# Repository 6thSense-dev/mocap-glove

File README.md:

# 6thSense magnetic MoCap glove

STM32G474 diagnostic/streaming firmware and local magnetic fingertip tracking viewer.

## Run locally

Install Python dependencies with `python3 -m pip install -r requirements.txt`, then run `python3 control-panel/server.py` and open http://127.0.0.1:8775/hand.

Read START-HERE.txt before powered tests. Firmware build instructions are in firmware-app/BUILD.txt. The viewer does not automatically flash hardware.

## Saved scope and limitations

Includes firmware source, local viewer, calibration algorithms, automated tests and required vendor assets. Hardware-specific calibration profiles, recordings, flash backups and build outputs remain on the development machine and are intentionally excluded. An empty checkout requires its own calibration before calibrated tracking can be reproduced. Browser display preferences are local to the browser.

Jitter filtering, continuous mirror-branch tracking and reversible per-finger Z display correction are included. Z reversal is a display correction, not physical calibration. Magnetic mirror ambiguity and absolute accuracy are not established by software tests. IMU translation is experimental and drifts; CAD joint angles are inferred robot retargeting, not independently measured finger joints.

## Third-party assets

The Aero Hand Open meshes and URDF originate from Chestnut Robotics (formerly TetherIA), commit 7bb2f23485a7d440960c21046da642de132b7745, under CC BY-NC-SA 4.0. Preserve the license, attribution and provenance in control-panel/vendor/aero-hand/. The current integration is for the user-confirmed noncommercial use. This is not a blanket license for commercial use of those assets.

Three.js and ST firmware dependencies retain their upstream license files. No blanket license is granted over the entire repository.

## Tests

`python3 -m unittest discover -s control-panel -p 'test_*.py'`

`node control-panel/test-hand-z-reflection.cjs`

`node control-panel/test-aero-kinematics.cjs`

`node control-panel/test-hand-view-frame.cjs`

## PCB design files

[Complete V6 PCB projects and manufacturing files](hardware/pcb/v6/README.md): hand hub, fingertip flex and source carrier.

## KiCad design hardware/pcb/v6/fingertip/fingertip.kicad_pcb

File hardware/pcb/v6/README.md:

# V6 PCB design archive

Complete current V6 project files for the hand hub, fingertip flex board and source carrier. Open each folder's `.kicad_pro` in KiCad 9. Custom symbols, footprints and envelope models are included; standard 3D models require KiCad's standard model library.

Each board includes schematics, routed PCB, project settings, local libraries, BOM, placement CSV, Gerber/drill files and ZIP, fabrication notes, rendered views and historical ERC/DRC reports. Source-carrier is included as a design artifact; it is not proof of the current hand-wound coil assembly configuration.

This is an archive of the existing V6 design, not a new engineering release or a renewed validation. Historical notes and reports reflect their original dates. In particular, the fingertip fabrication data specifies 0.40 mm FR4 stiffening; confirm the manufacturer-approved stackup before reordering. Do not infer measured tracking accuracy or factory acceptance from these files.

Order/checkout records, private contact details, editor state, obsolete V1–V5 designs and software recordings are excluded. Only machine-specific paths in exported verification netlists were made relative; electrical design and manufacturing files are unchanged. FILE-MANIFEST.json records SHA-256 hashes of the published files.

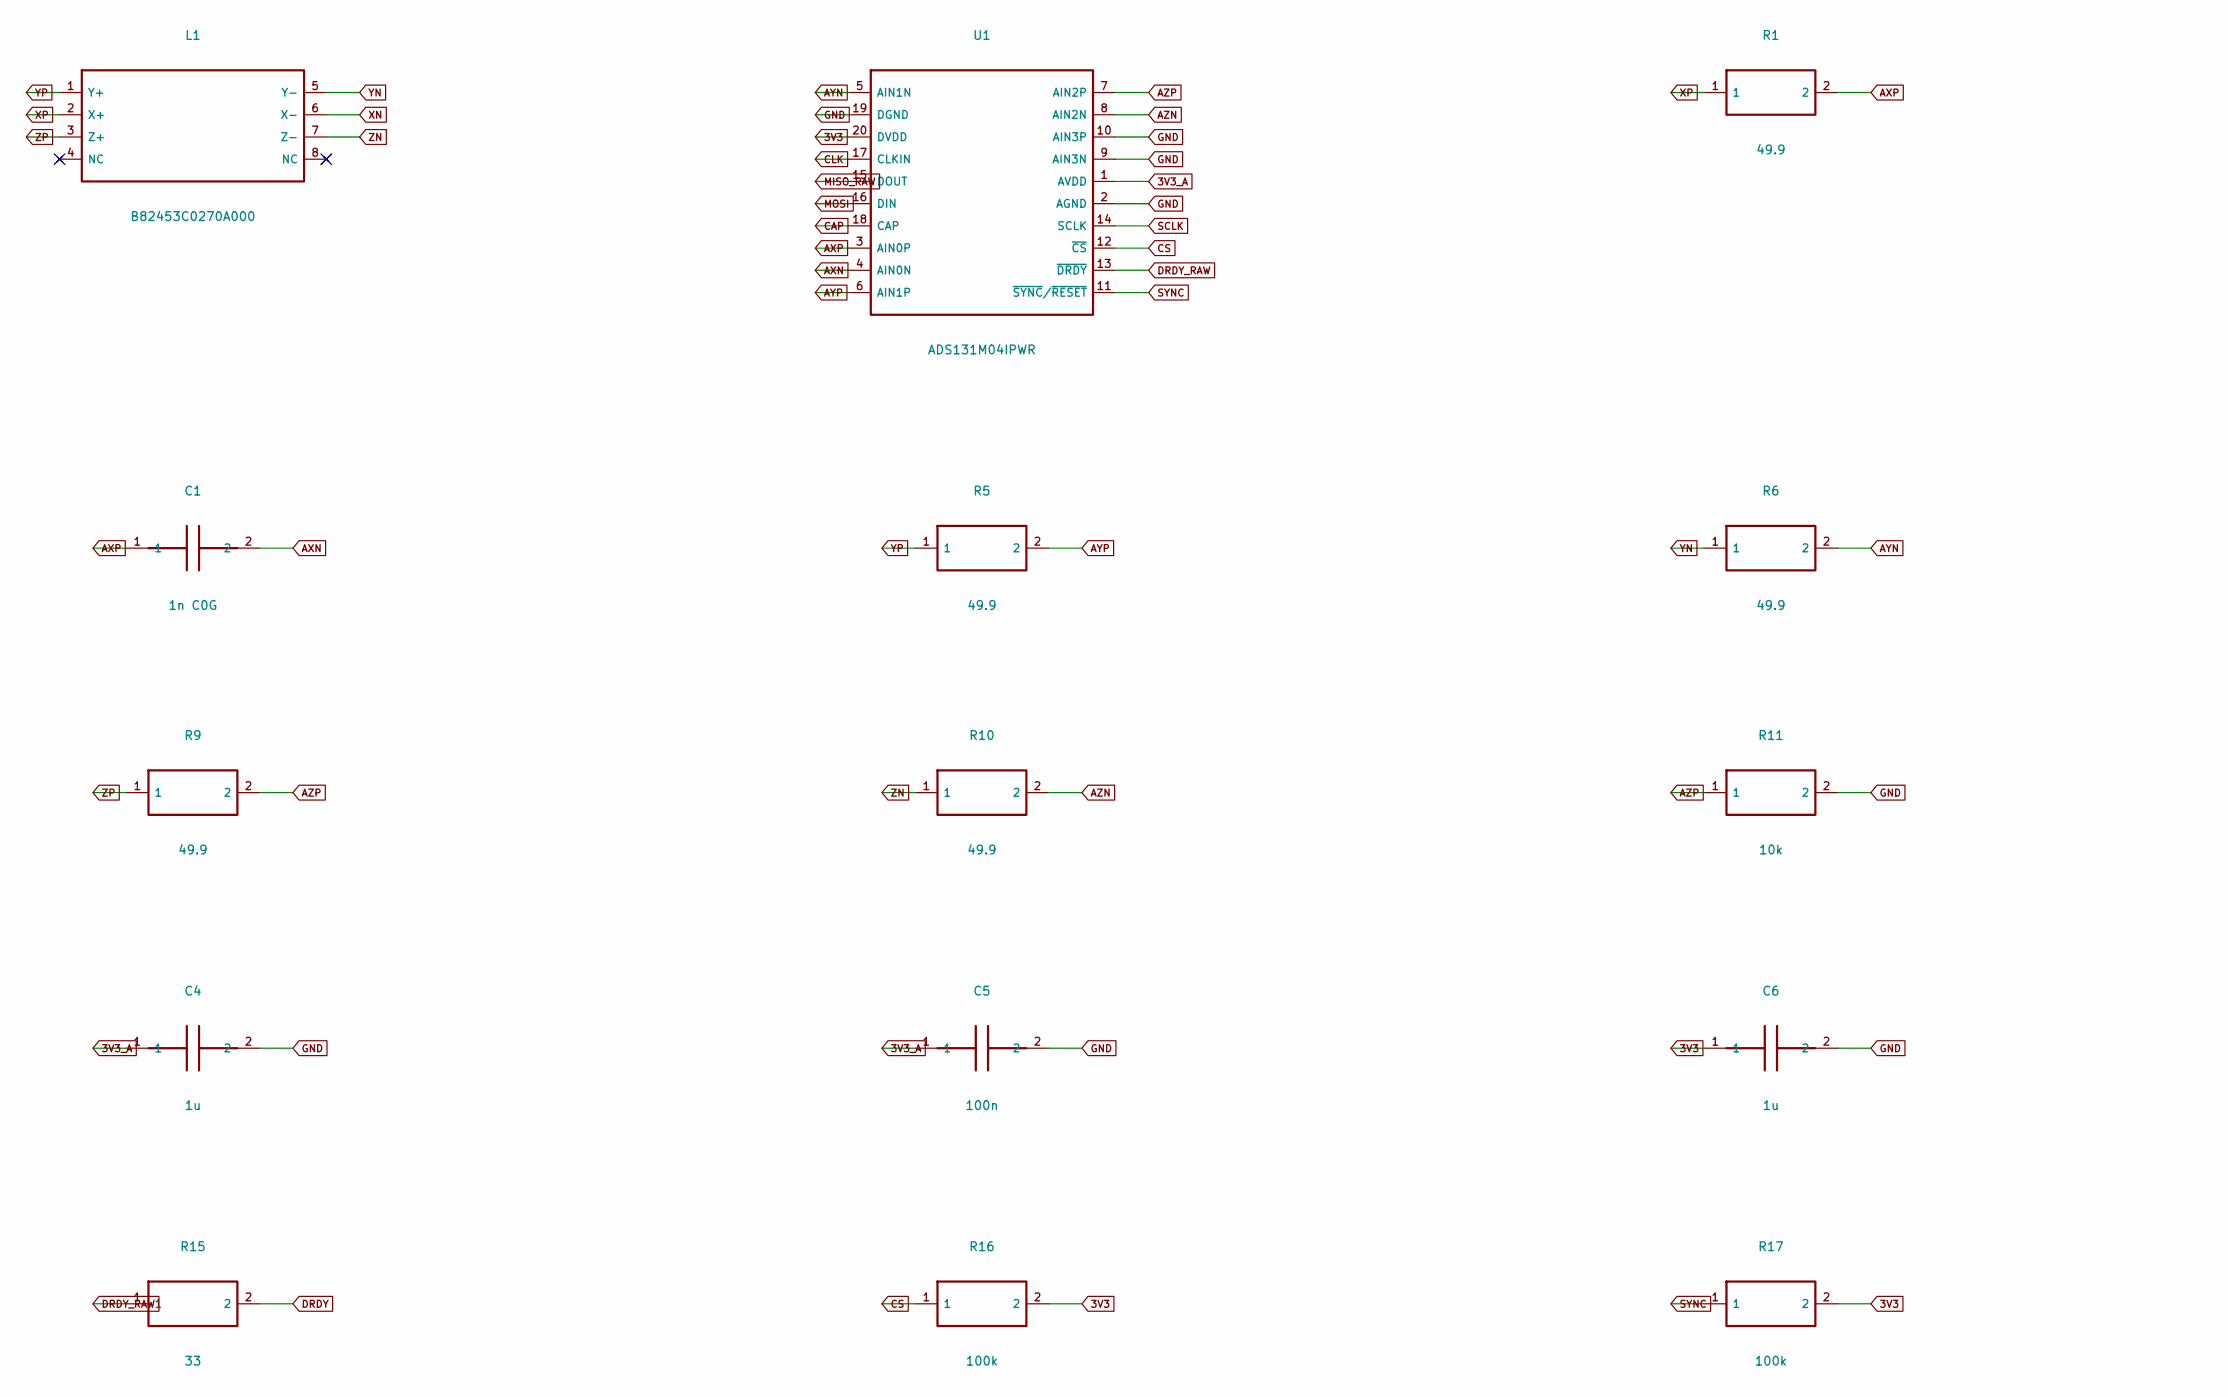
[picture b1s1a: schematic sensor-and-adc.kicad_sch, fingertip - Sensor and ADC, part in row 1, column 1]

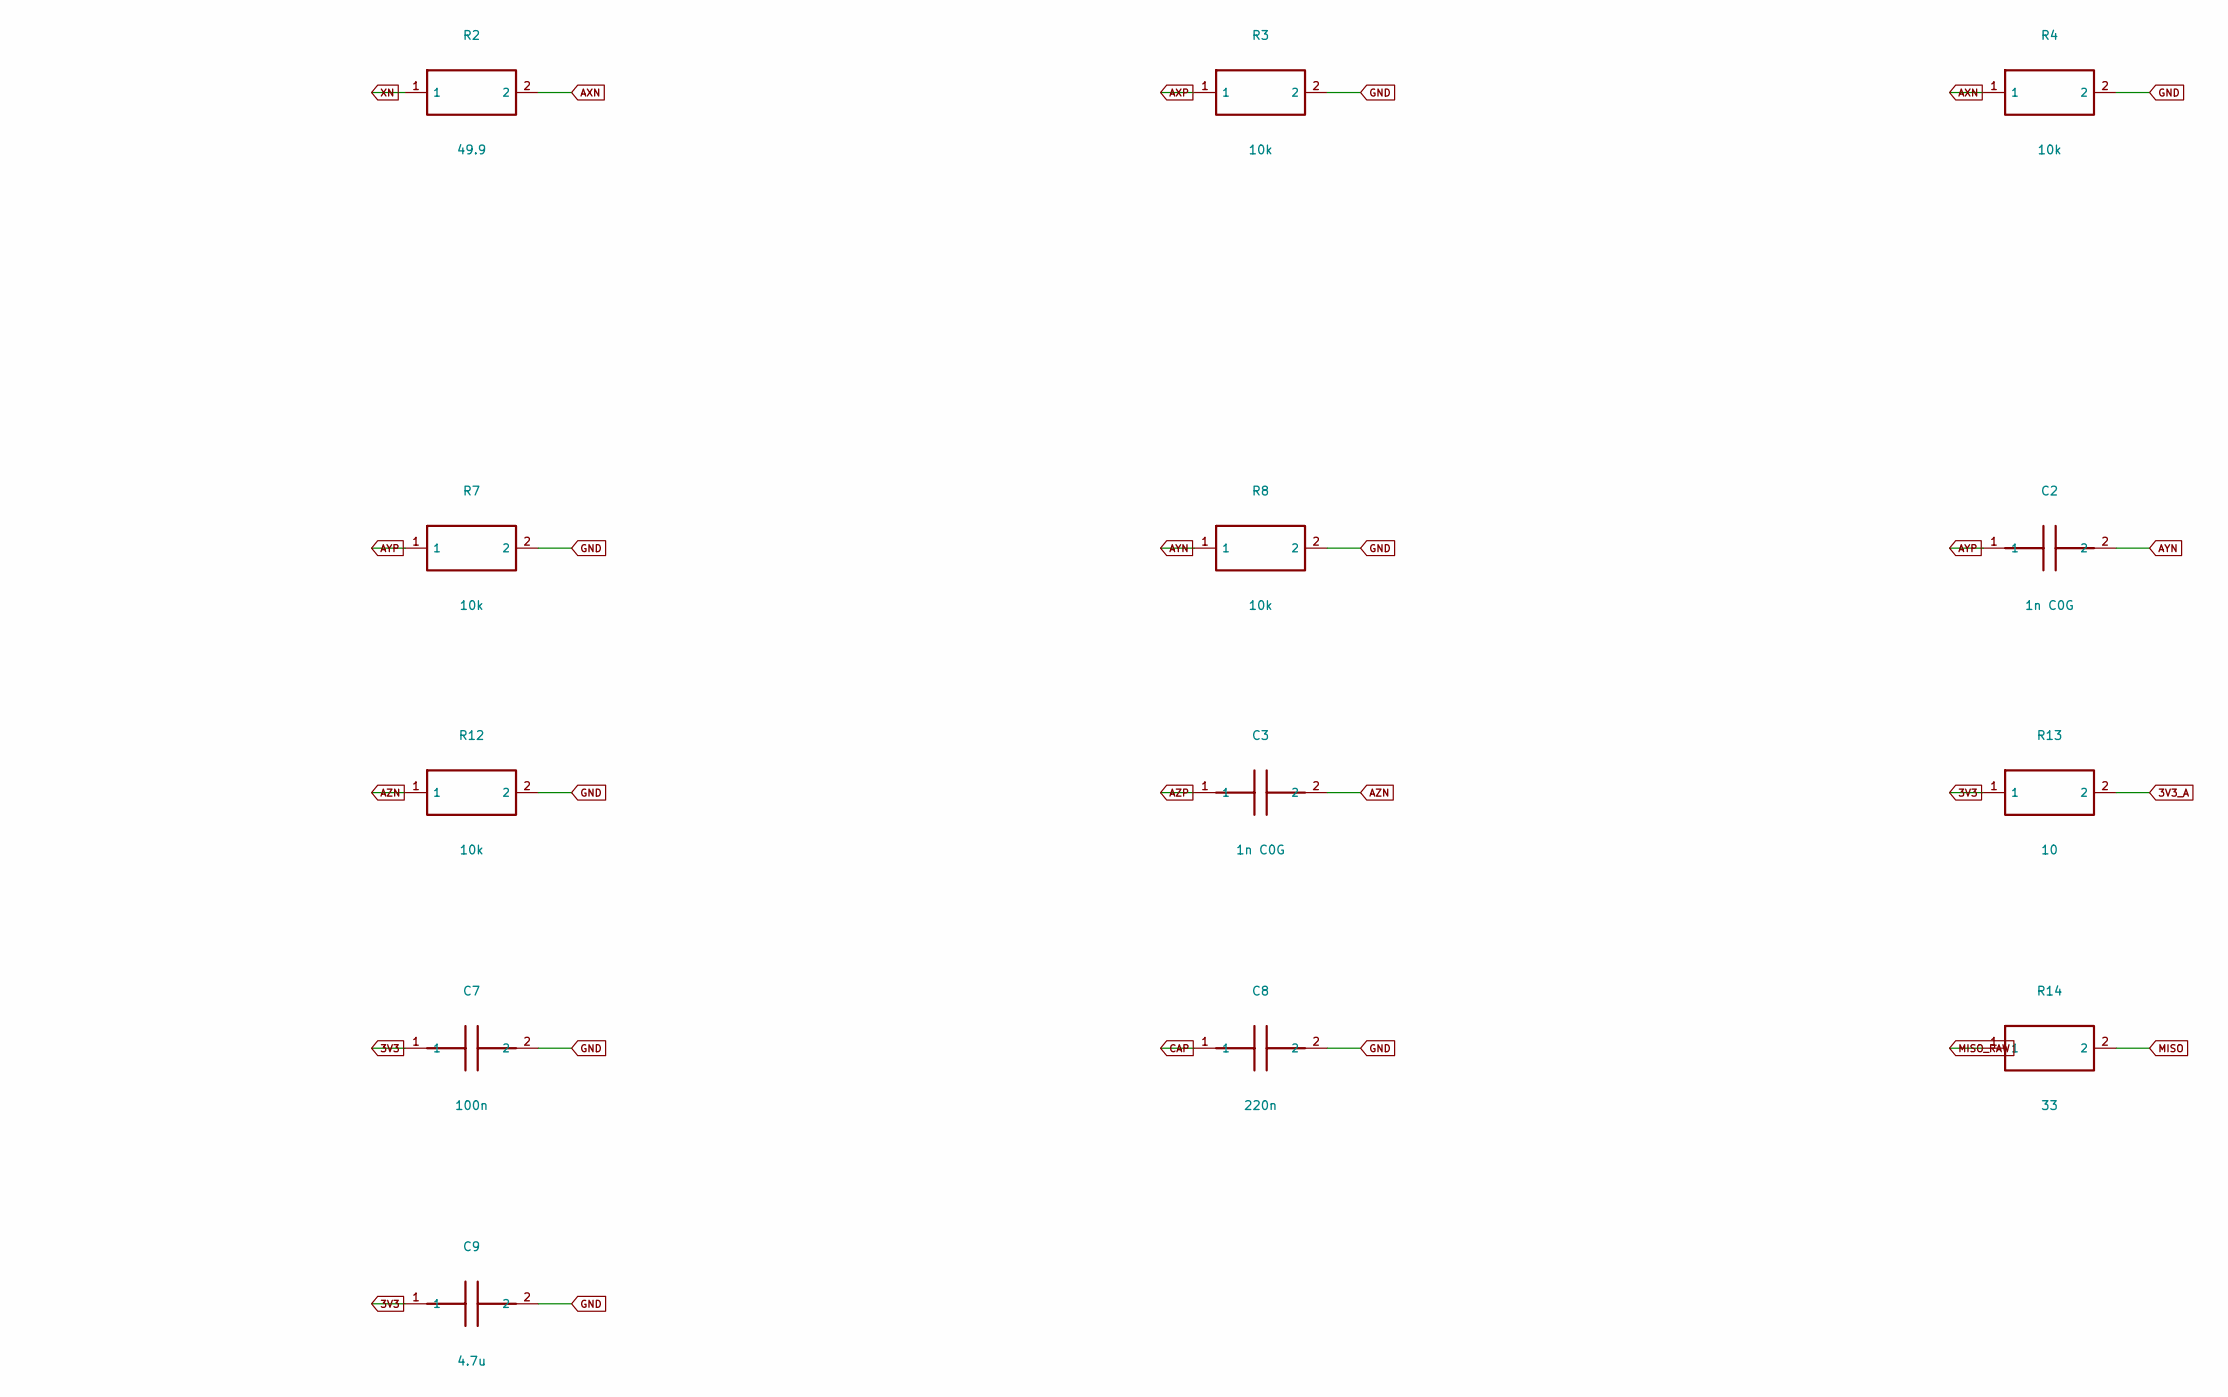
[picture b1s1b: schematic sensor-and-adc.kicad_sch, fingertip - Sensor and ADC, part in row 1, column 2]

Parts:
C1, C2, C3: 1n C0G; C_0402_1005Metric; MPN 1n C0G
C4, C6: 1u; C_0402_1005Metric; MPN 1u
C5, C7: 100n; C_0402_1005Metric; MPN 100n
C8: 220n; C_0402_1005Metric; MPN 220n
C9: 4.7u; C_0402_1005Metric; MPN 4.7u
L1: B82453C0270A000; TDK_3D; MPN B82453C0270A000
R1, R2, R5, R6, R9, R10: 49.9; R_0402_1005Metric; MPN 49.9
R3, R4, R7, R8, R11, R12: 10k; R_0402_1005Metric; MPN 10k
R13: 10; R_0402_1005Metric; MPN 10
R14, R15: 33; R_0402_1005Metric; MPN 33
R16, R17: 100k; R_0402_1005Metric; MPN 100k
U1: ADS131M04IPWR; TSSOP-20_4.4x6.5mm_P0.65mm; MPN ADS131M04IPWR

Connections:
3V3: C6.1, C7.1, C9.1, R13.1, R16.2, R17.2, U1.20 (DVDD); also elsewhere on the board
3V3_A: C4.1, C5.1, R13.2, U1.1 (AVDD)
AXN: C1.2, R2.2, R4.1, U1.4 (AIN0N)
AXP: C1.1, R1.2, R3.1, U1.3 (AIN0P)
AYN: C2.2, R6.2, R8.1, U1.5 (AIN1N)
AYP: C2.1, R5.2, R7.1, U1.6 (AIN1P)
AZN: C3.2, R10.2, R12.1, U1.8 (AIN2N)
AZP: C3.1, R9.2, R11.1, U1.7 (AIN2P)
CAP: C8.1, U1.18 (CAP)
CLK: U1.17 (CLKIN); also elsewhere on the board
CS: R16.1, U1.12 (~CS); also elsewhere on the board
DRDY: R15.2; also elsewhere on the board
DRDY_RAW: R15.1, U1.13 (~DRDY)
GND: C4.2, C5.2, C6.2, C7.2, C8.2, C9.2, R3.2, R4.2, R7.2, R8.2, R11.2, R12.2, U1.2 (AGND), U1.9 (AIN3N), U1.10 (AIN3P), U1.19 (DGND); also elsewhere on the board
MISO: R14.2; also elsewhere on the board
MISO_RAW: R14.1, U1.15 (DOUT)
MOSI: U1.16 (DIN); also elsewhere on the board
SCLK: U1.14 (SCLK); also elsewhere on the board
SYNC: R17.1, U1.11 (~SYNC/~RESET); also elsewhere on the board
XN: L1.6 (X-), R2.1
XP: L1.2 (X+), R1.1
YN: L1.5 (Y-), R6.1
YP: L1.1 (Y+), R5.1
ZN: L1.7 (Z-), R10.1
ZP: L1.3 (Z+), R9.1

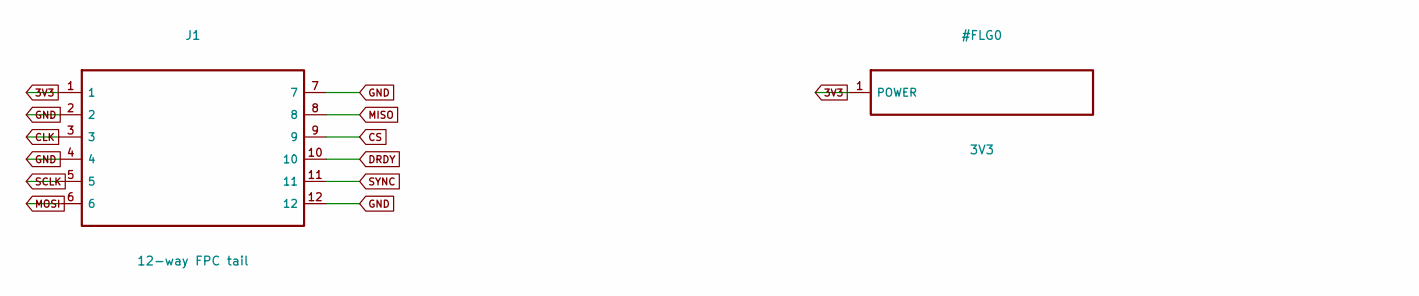
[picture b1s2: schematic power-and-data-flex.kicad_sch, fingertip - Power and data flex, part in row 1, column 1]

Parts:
J1: 12-way FPC tail; Tail12; MPN 12-way FPC tail

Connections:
3V3: J1.1; also elsewhere on the board
CLK: J1.3; also elsewhere on the board
CS: J1.9; also elsewhere on the board
DRDY: J1.10; also elsewhere on the board
GND: J1.2, J1.4, J1.7, J1.12; also elsewhere on the board
MISO: J1.8; also elsewhere on the board
MOSI: J1.6; also elsewhere on the board
SCLK: J1.5; also elsewhere on the board
SYNC: J1.11; also elsewhere on the board

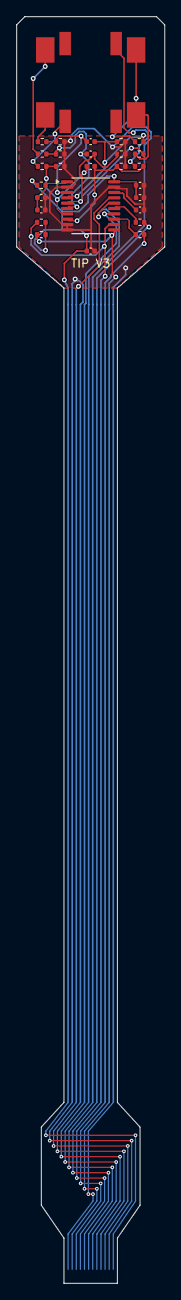
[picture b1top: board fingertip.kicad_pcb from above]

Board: 2 copper layers, 18.0 x 154.0 mm, 29 parts (0 on the bottom side), 25 nets.

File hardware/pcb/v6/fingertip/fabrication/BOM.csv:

Comment,Designator,Footprint,LCSC Part #
ADS131M04IPWR,U1,TSSOP-20_4.4x6.5mm_P0.65mm,C2862562
49.9,"R1,R10,R2,R5,R6,R9",R_0402_1005Metric,C87044
10k,"R11,R12,R3,R4,R7,R8",R_0402_1005Metric,C25744
1n C0G,"C1,C2,C3",C_0402_1005Metric,C307441
10,R13,R_0402_1005Metric,C25077
1u,"C4,C6",C_0402_1005Metric,C52923
100n,"C5,C7",C_0402_1005Metric,C1525
220n,C8,C_0402_1005Metric,C16772
33,"R14,R15",R_0402_1005Metric,C25105
100k,"R16,R17",R_0402_1005Metric,C25741
4.7u,C9,C_0402_1005Metric,C23733

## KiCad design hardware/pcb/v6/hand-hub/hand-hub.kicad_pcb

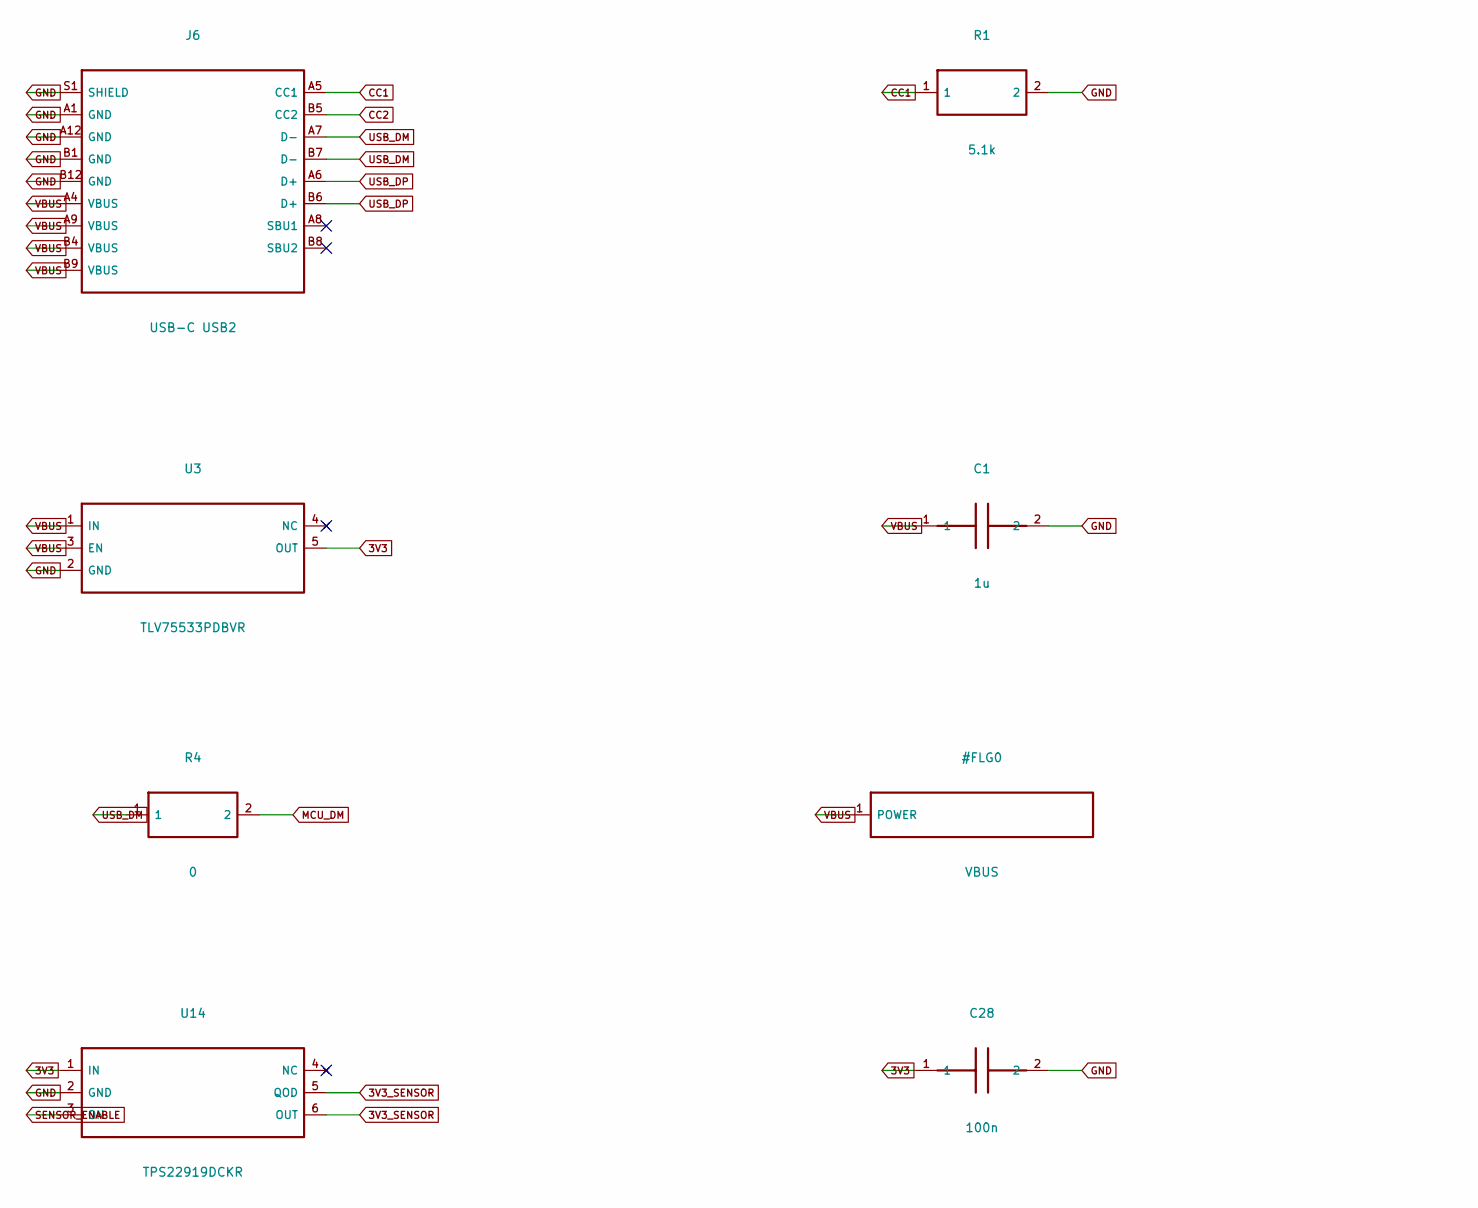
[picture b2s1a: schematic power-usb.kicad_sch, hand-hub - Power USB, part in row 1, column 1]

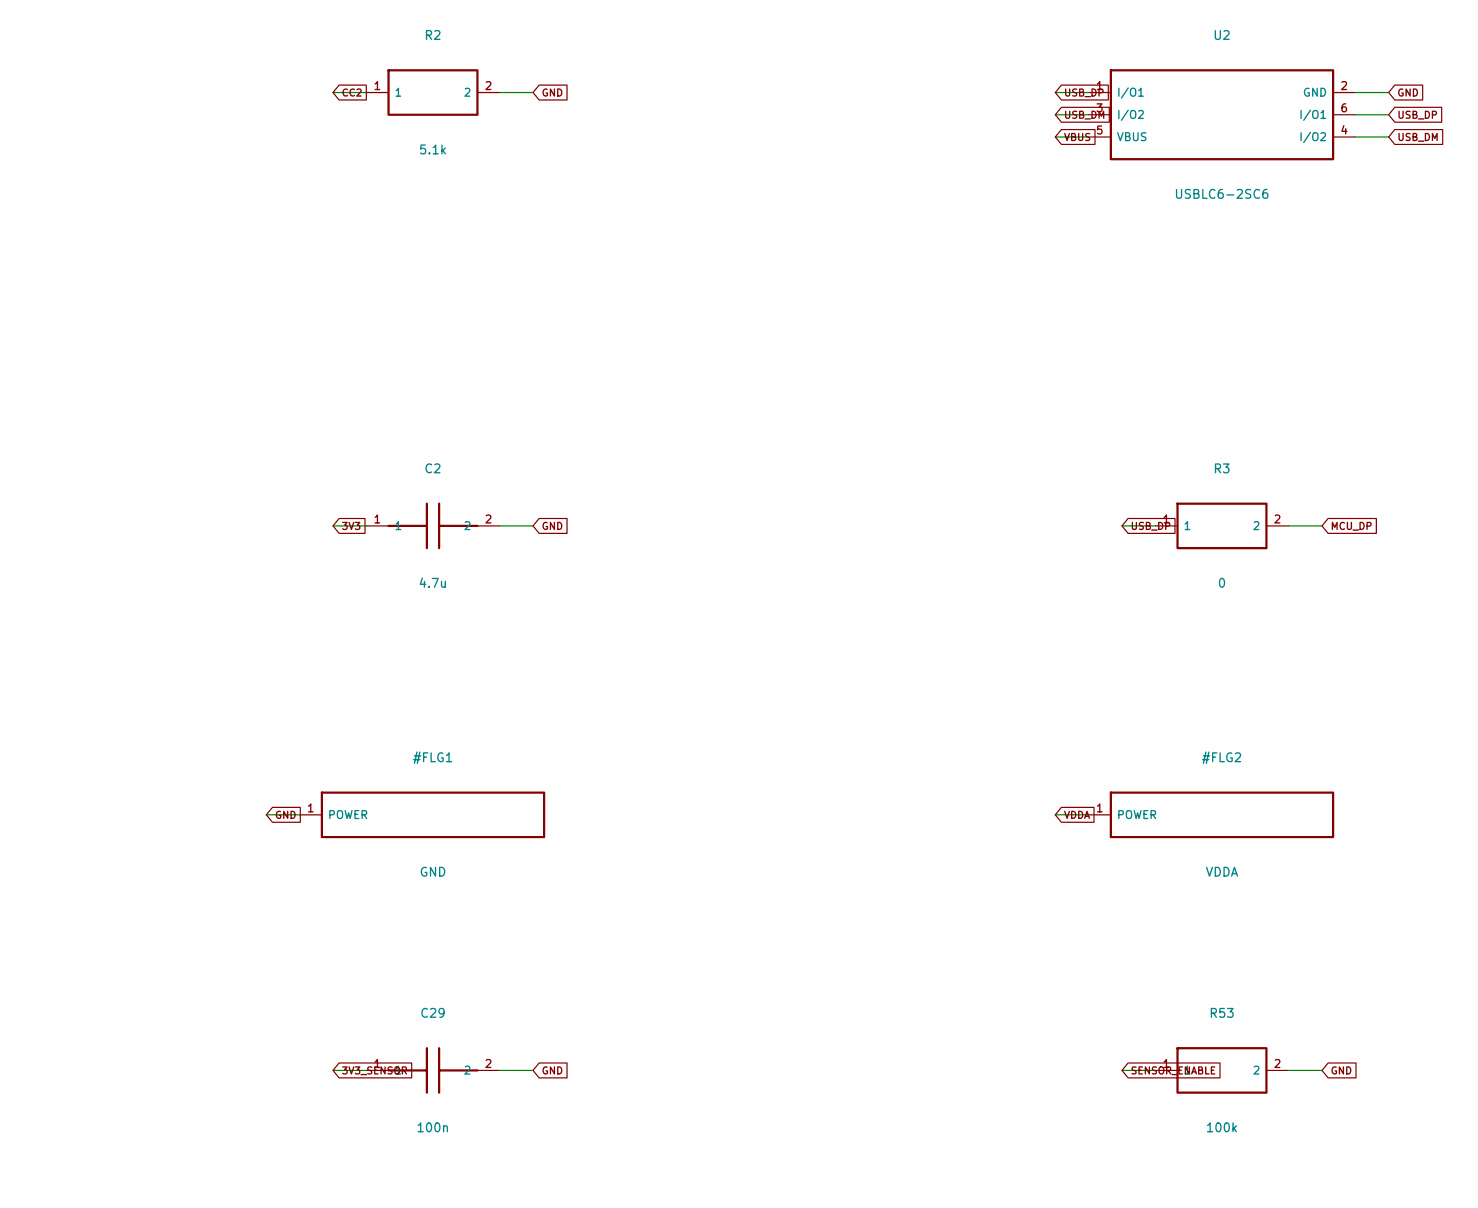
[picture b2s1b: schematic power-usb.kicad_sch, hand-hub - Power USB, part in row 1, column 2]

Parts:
C1: 1u; C_0603_1608Metric; MPN 1u
C2: 4.7u; C_0603_1608Metric; MPN 4.7u
C28, C29: 100n; C_0402_1005Metric; MPN 100n
J6: USB-C USB2; USB_C_HRO_Envelope; MPN TYPE-C-31-M-12
R1, R2: 5.1k; R_0603_1608Metric; MPN 5.1k
R3, R4: 0; R_0603_1608Metric; MPN 0603WAF0000T5E
R53: 100k; R_0402_1005Metric; MPN 100k
U2: USBLC6-2SC6; SOT-23-6; MPN USBLC6-2SC6
U3: TLV75533PDBVR; SOT-23-5; MPN TLV75533PDBVR
U14: TPS22919DCKR; SOT-363_SC-70-6; MPN TPS22919DCKR

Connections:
3V3: C2.1, C28.1, U3.5 (OUT), U14.1 (IN); also elsewhere on the board
3V3_SENSOR: C29.1, U14.5 (QOD), U14.6 (OUT); also elsewhere on the board
CC1: J6.A5 (CC1), R1.1
CC2: J6.B5 (CC2), R2.1
GND: C1.2, C2.2, C28.2, C29.2, J6.A1 (GND), J6.A12 (GND), J6.B1 (GND), J6.B12 (GND), J6.S1 (SHIELD), R1.2, R2.2, R53.2, U2.2 (GND), U3.2 (GND), U14.2 (GND); also elsewhere on the board
MCU_DM: R4.2; also elsewhere on the board
MCU_DP: R3.2; also elsewhere on the board
SENSOR_ENABLE: R53.1, U14.3 (ON); also elsewhere on the board
USB_DM: J6.A7 (D-), J6.B7 (D-), R4.1, U2.3 (I/O2), U2.4 (I/O2)
USB_DP: J6.A6 (D+), J6.B6 (D+), R3.1, U2.1 (I/O1), U2.6 (I/O1)
VBUS: C1.1, J6.A4 (VBUS), J6.A9 (VBUS), J6.B4 (VBUS), J6.B9 (VBUS), U2.5 (VBUS), U3.1 (IN), U3.3 (EN); also elsewhere on the board

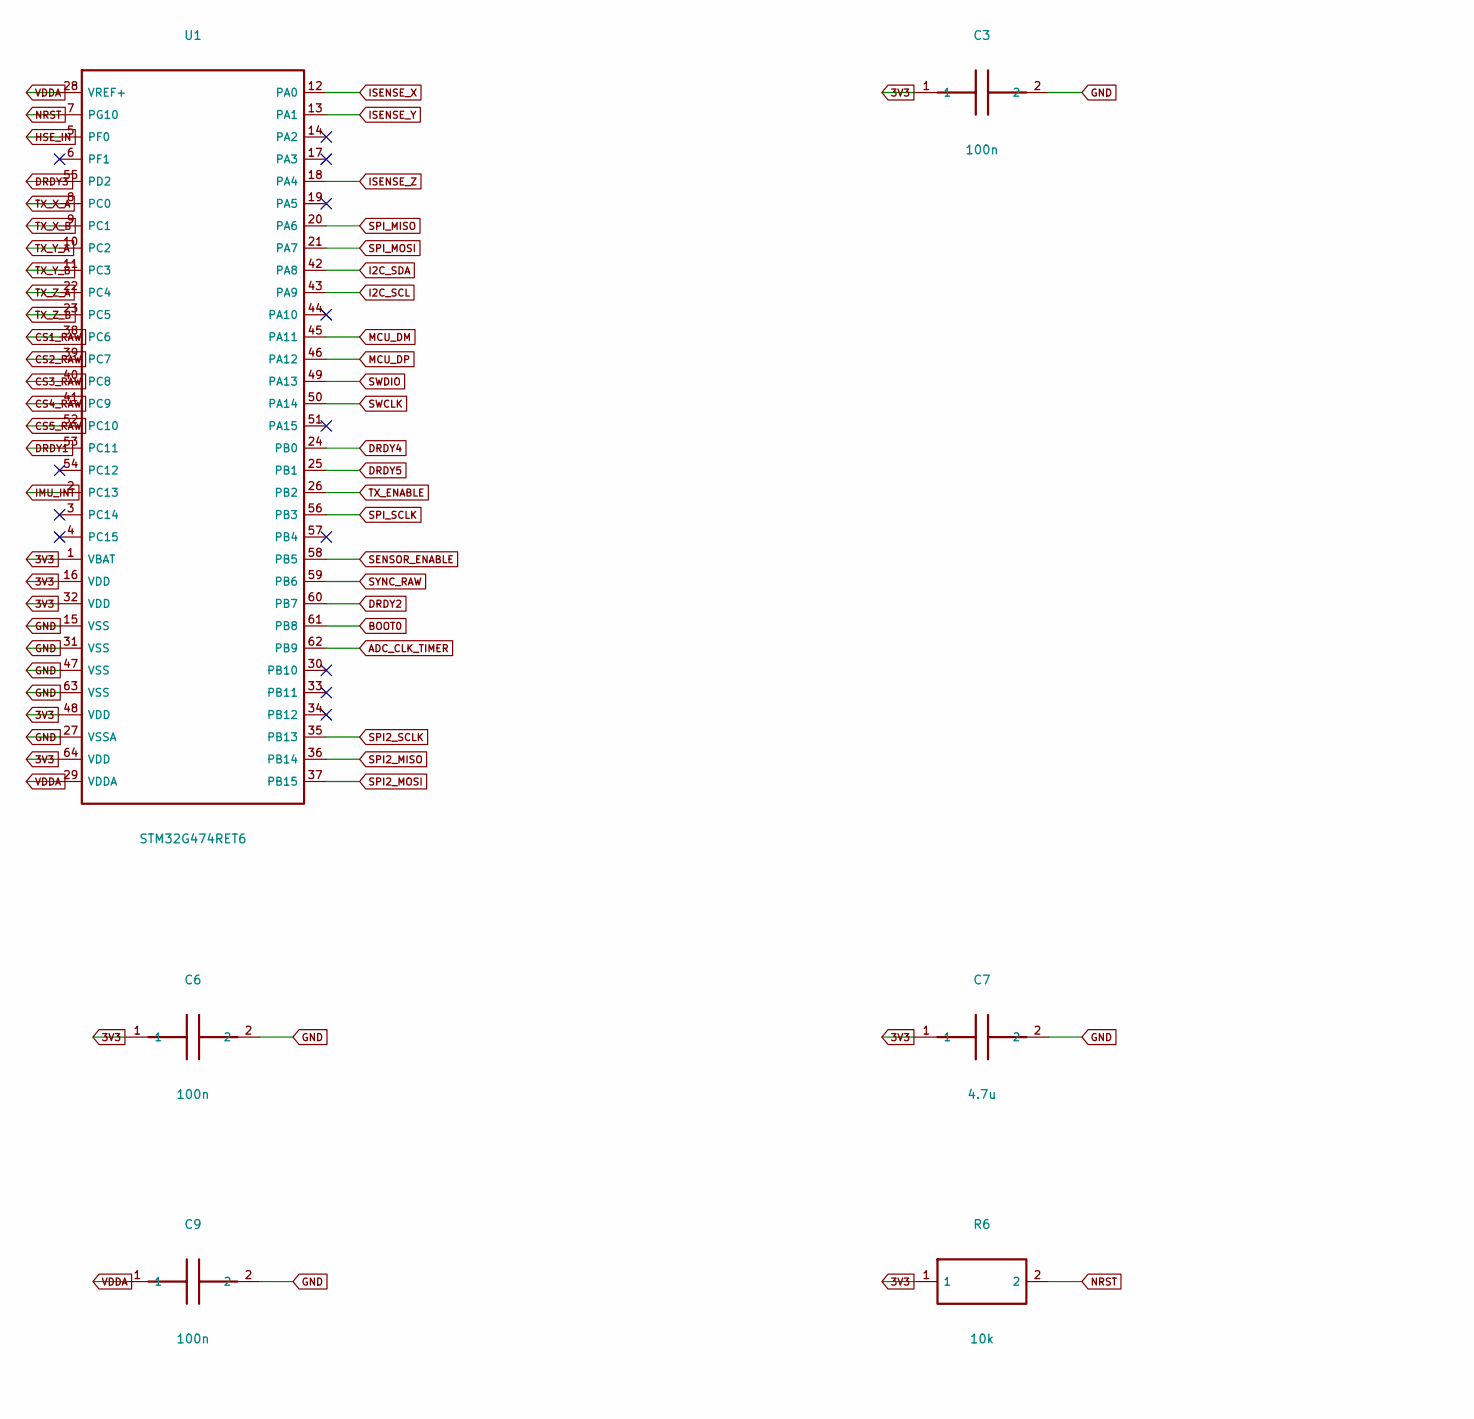
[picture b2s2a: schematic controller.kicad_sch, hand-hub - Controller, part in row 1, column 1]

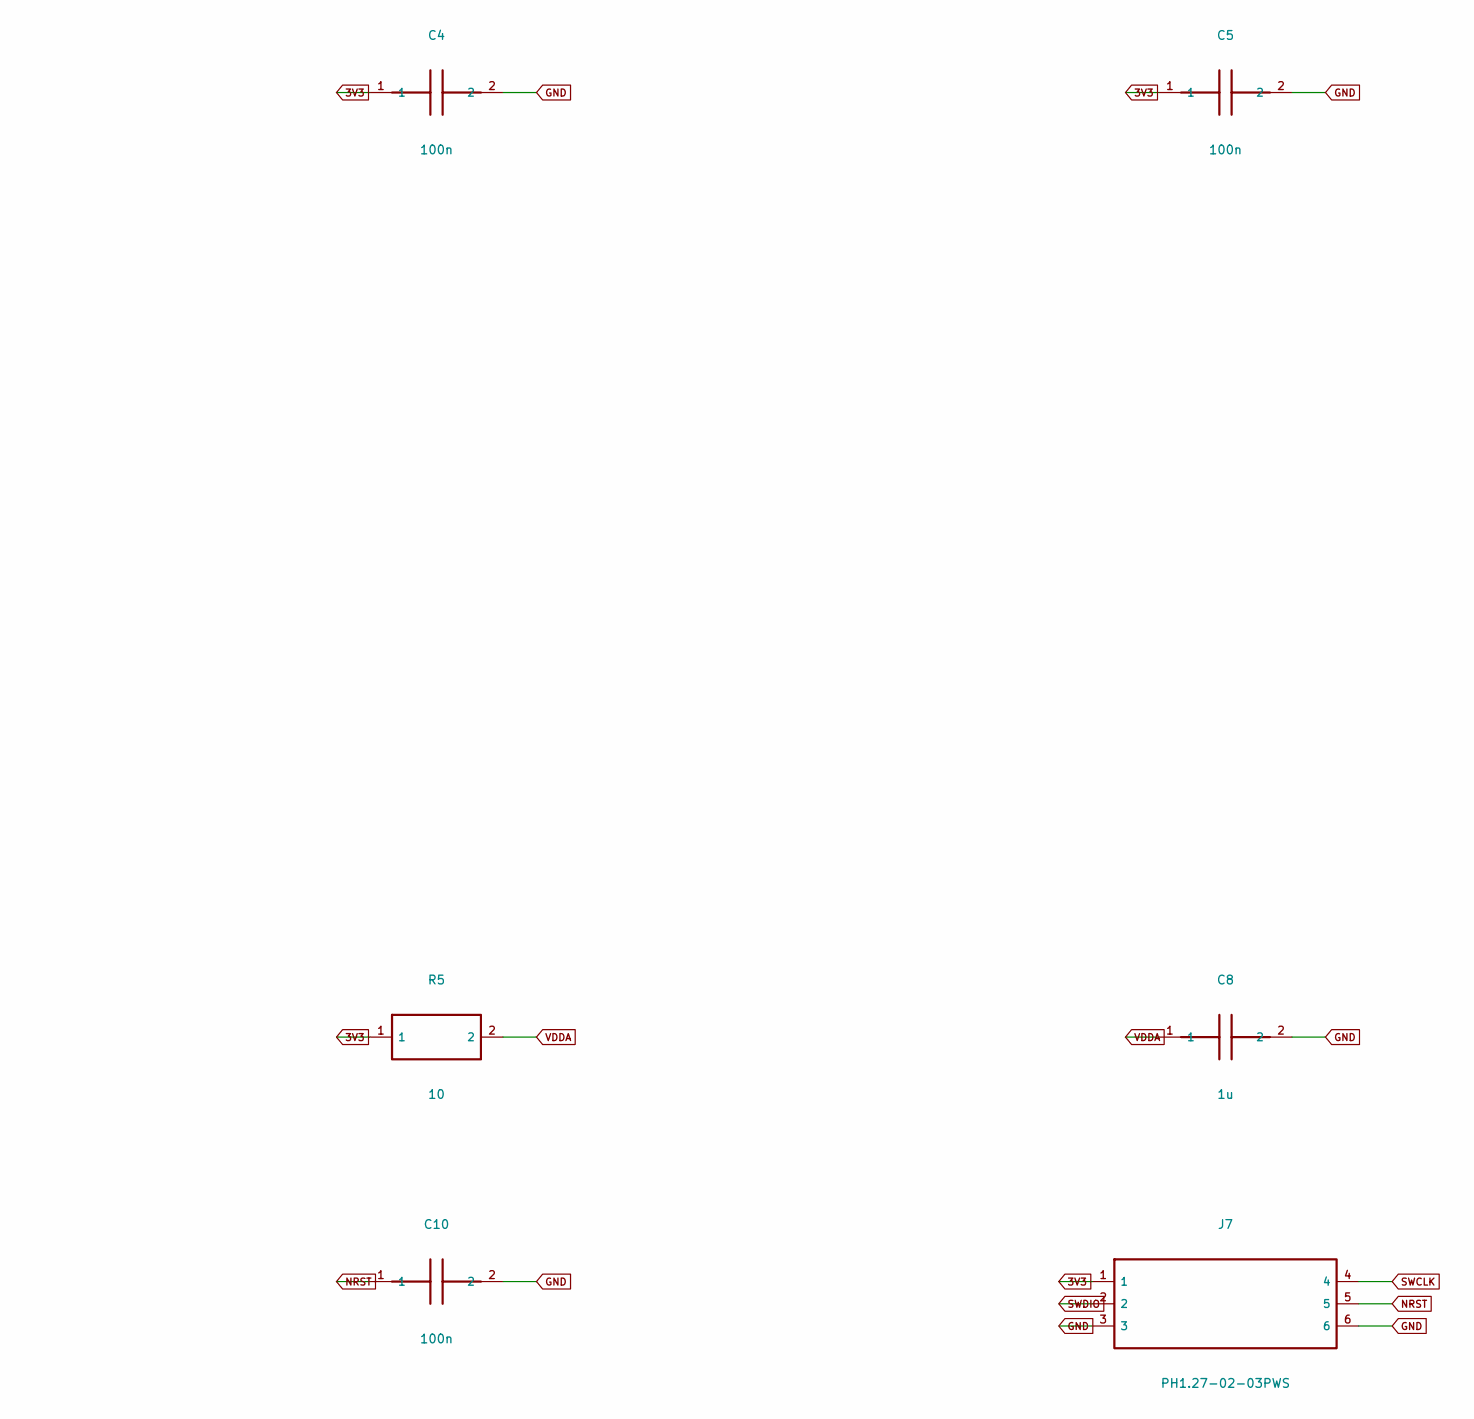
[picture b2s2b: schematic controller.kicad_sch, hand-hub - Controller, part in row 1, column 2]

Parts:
C3, C4, C5, C6, C9, C10: 100n; C_0402_1005Metric; MPN 100n
C7: 4.7u; C_0402_1005Metric; MPN 4.7u
C8: 1u; C_0402_1005Metric; MPN 1u
J7: PH1.27-02-03PWS; XUNPU_PH127_2x03_SMD; MPN PH1.27-02-03PWS
R5: 10; R_0402_1005Metric; MPN 10
R6: 10k; R_0402_1005Metric; MPN 10k
U1: STM32G474RET6; LQFP-64_10x10mm_P0.5mm; MPN STM32G474RET6

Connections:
3V3: C3.1, C4.1, C5.1, C6.1, C7.1, J7.1, R5.1, R6.1, U1.1 (VBAT), U1.16 (VDD), U1.32 (VDD), U1.48 (VDD), U1.64 (VDD); also elsewhere on the board
ADC_CLK_TIMER: U1.62 (PB9); also elsewhere on the board
BOOT0: U1.61 (PB8); also elsewhere on the board
CS1_RAW: U1.38 (PC6); also elsewhere on the board
CS2_RAW: U1.39 (PC7); also elsewhere on the board
CS3_RAW: U1.40 (PC8); also elsewhere on the board
CS4_RAW: U1.41 (PC9); also elsewhere on the board
CS5_RAW: U1.52 (PC10); also elsewhere on the board
DRDY1: U1.53 (PC11); also elsewhere on the board
DRDY2: U1.60 (PB7); also elsewhere on the board
DRDY3: U1.55 (PD2); also elsewhere on the board
DRDY4: U1.24 (PB0); also elsewhere on the board
DRDY5: U1.25 (PB1); also elsewhere on the board
GND: C3.2, C4.2, C5.2, C6.2, C7.2, C8.2, C9.2, C10.2, J7.3, J7.6, U1.15 (VSS), U1.27 (VSSA), U1.31 (VSS), U1.47 (VSS), U1.63 (VSS); also elsewhere on the board
HSE_IN: U1.5 (PF0); also elsewhere on the board
I2C_SCL: U1.43 (PA9); also elsewhere on the board
I2C_SDA: U1.42 (PA8); also elsewhere on the board
IMU_INT: U1.2 (PC13); also elsewhere on the board
ISENSE_X: U1.12 (PA0); also elsewhere on the board
ISENSE_Y: U1.13 (PA1); also elsewhere on the board
ISENSE_Z: U1.18 (PA4); also elsewhere on the board
MCU_DM: U1.45 (PA11); also elsewhere on the board
MCU_DP: U1.46 (PA12); also elsewhere on the board
NRST: C10.1, J7.5, R6.2, U1.7 (PG10); also elsewhere on the board
SENSOR_ENABLE: U1.58 (PB5); also elsewhere on the board
SPI2_MISO: U1.36 (PB14); also elsewhere on the board
SPI2_MOSI: U1.37 (PB15); also elsewhere on the board
SPI2_SCLK: U1.35 (PB13); also elsewhere on the board
SPI_MISO: U1.20 (PA6); also elsewhere on the board
SPI_MOSI: U1.21 (PA7); also elsewhere on the board
SPI_SCLK: U1.56 (PB3); also elsewhere on the board
SWCLK: J7.4, U1.50 (PA14)
SWDIO: J7.2, U1.49 (PA13)
SYNC_RAW: U1.59 (PB6); also elsewhere on the board
TX_ENABLE: U1.26 (PB2); also elsewhere on the board
TX_X_A: U1.8 (PC0); also elsewhere on the board
TX_X_B: U1.9 (PC1); also elsewhere on the board
TX_Y_A: U1.10 (PC2); also elsewhere on the board
TX_Y_B: U1.11 (PC3); also elsewhere on the board
TX_Z_A: U1.22 (PC4); also elsewhere on the board
TX_Z_B: U1.23 (PC5); also elsewhere on the board
VDDA: C8.1, C9.1, R5.2, U1.28 (VREF+), U1.29 (VDDA)
